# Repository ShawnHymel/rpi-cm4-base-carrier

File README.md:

# Raspberry Pi Compute Module 4 (CM4) Base Carrier

Simple carrier board for the Raspberry Pi Compute Module 4. It provides power to the module through the USB-C connector (power only, no data), USB client mode (host mode is not supported), Qwiic/Stemma connector for I2C lines, SPI, UART, and power/activity LEDs.

Feel free to modify this design for your own application. This PCB is not intended to be an end product but rather a demo to get people started making their own carrier boards for the CM4.

Note that USB traces were calculated for a 2-layer board with a 1.6mm height.

## License

Schematic and PCB layout files are licensed under the [CC BY 4.0](https://creativecommons.org/licenses/by/2.0/) license.

Individual components and footprints found in the CM4IO library are licensed as per the Design Files license found [here](https://datasheets.raspberrypi.org/license.html).

THE DESIGN IS PROVIDED "AS IS" AND THE AUTHOR DISCLAIMS ALL WARRANTIES WITH REGARD TO THIS DESIGN INCLUDING ALL IMPLIED WARRANTIES OF MERCHANTABILITY AND FITNESS. IN NO EVENT SHALL THE AUTHOR BE LIABLE FOR ANY SPECIAL, DIRECT, INDIRECT, OR CONSEQUENTIAL DAMAGES OR ANY DAMAGES WHATSOEVER RESULTING FROM LOSS OF USE, DATA OR PROFITS, WHETHER IN AN ACTION OF CONTRACT, NEGLIGENCE OR OTHER TORTIOUS ACTION, ARISING OUT OF OR IN CONNECTION WITH THE USE OR PERFORMANCE OF THIS DESIGN.

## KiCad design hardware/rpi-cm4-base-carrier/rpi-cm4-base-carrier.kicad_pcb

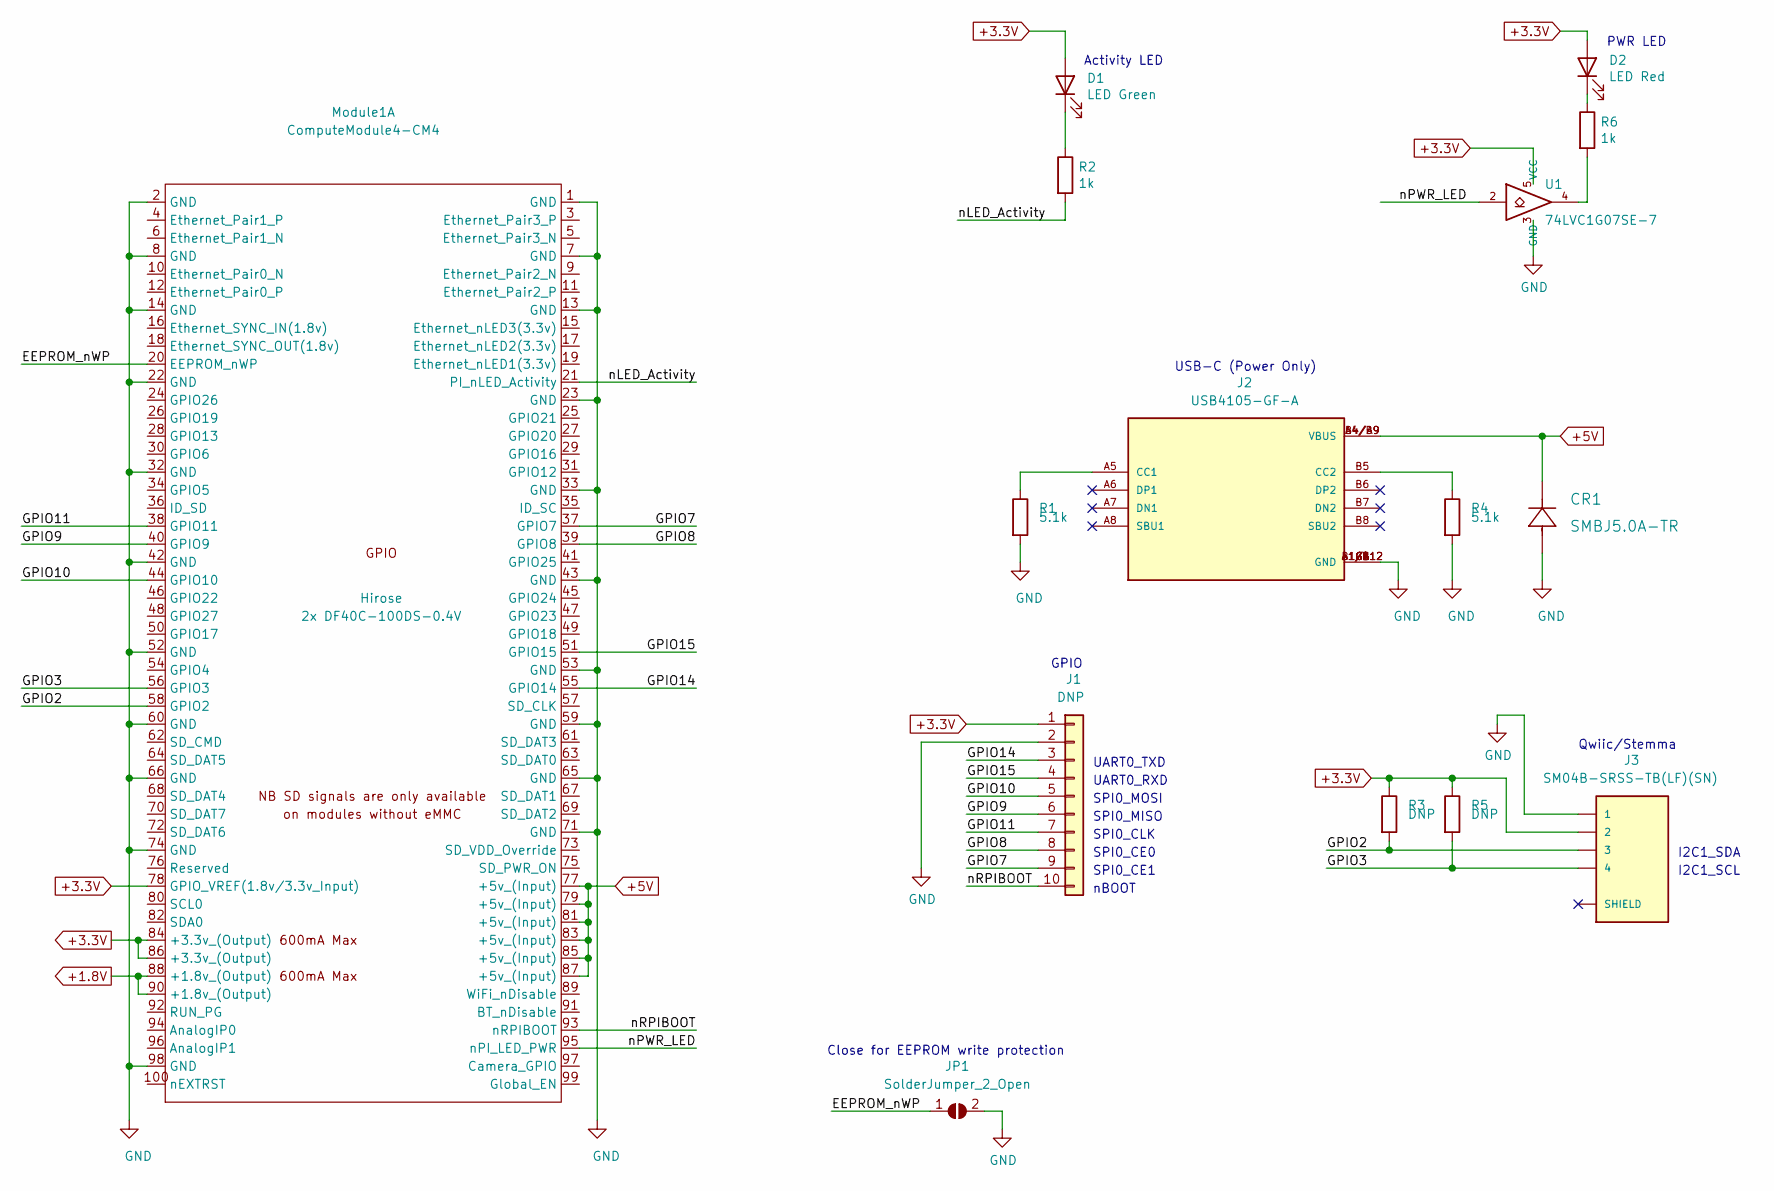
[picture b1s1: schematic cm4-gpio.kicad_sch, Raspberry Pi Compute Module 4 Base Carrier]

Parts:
CR1: SMBJ5.0A-TR; MPN SMBJ5.0A-TR; Digi-Key_PN 497-3144-1-ND
D1: LED Green; LED_0603_1608Metric; Part Description Green 572nm LED Indication - Discrete 2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; Digi-Key_PN 160-1478-1-ND
D2: LED Red; LED_0603_1608Metric; Part Description Red 620nm LED Indication - Discrete 2.2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; Digi-Key_PN 160-1479-1-ND
J1: DNP; PinHeader_1x10_P2.54mm_Vertical
J2: USB4105-GF-A; GCT_USB4105-GF-A; MPN USB4105-GF-A; Digi-Key_PN 2073-USB4105-GF-ACT-ND
J3: SM04B-SRSS-TB(LF)(SN); JST_SM04B-SRSS-TB(LF)(SN); MPN SM04B-SRSS-TB(LF)(SN); Digi-Key_PN 455-1804-1-ND
JP1: SolderJumper_2_Open; SolderJumper-2_P1.3mm_Open_RoundedPad1.0x1.5mm
Module1: ComputeModule4-CM4; Raspberry-Pi-4-Compute-Module; MPN 2x DF40C-100DS-0.4V; Digi-Key_PN 2x H11615CT-ND
R1, R4: 5.1k; R_0603_1608Metric_Pad0.98x0.95mm_HandSolder; MPN RC0603FR-075K1L; Digi-Key_PN 311-5.10KHRCT-ND
R2, R6: 1k; R_0603_1608Metric_Pad0.98x0.95mm_HandSolder; MPN RC0603FR-071KL; Digi-Key_PN 311-1.00KHRCT-ND
R3, R5: DNP; R_0603_1608Metric_Pad0.98x0.95mm_HandSolder
U1: 74LVC1G07SE-7; SOT-353_SC-70-5; Part Description Buffer, Non-Inverting 1 Element 1 Bit p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; Digi-Key_PN 74LVC1G07SE-7DICT-ND

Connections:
+1.8V: Module1.88 (+1.8v_(Output)), Module1.90 (+1.8v_(Output))
+3.3V: D1.2 (A), D2.2 (A), J1.1, J3.2, Module1.78 (GPIO_VREF(1.8v/3.3v_Input)), Module1.84 (+3.3v_(Output)), Module1.86 (+3.3v_(Output)), R3.1, R5.1, U1.5 (VCC)
+5V: CR1.1, J2.A4/B9 (VBUS), J2.B4/A9 (VBUS), Module1.77 (+5v_(Input)), Module1.79 (+5v_(Input)), Module1.81 (+5v_(Input)), Module1.83 (+5v_(Input)), Module1.85 (+5v_(Input)), Module1.87 (+5v_(Input))
/CM4 GPIO/EEPROM_nWP: JP1.1 (A), Module1.20 (EEPROM_nWP)
/CM4 GPIO/GPIO2: J3.3, Module1.58 (GPIO2), R3.2
/CM4 GPIO/GPIO3: J3.4, Module1.56 (GPIO3), R5.2
/CM4 GPIO/GPIO7: J1.9, Module1.37 (GPIO7)
/CM4 GPIO/GPIO8: J1.8, Module1.39 (GPIO8)
/CM4 GPIO/GPIO9: J1.6, Module1.40 (GPIO9)
/CM4 GPIO/GPIO10: J1.5, Module1.44 (GPIO10)
/CM4 GPIO/GPIO11: J1.7, Module1.38 (GPIO11)
/CM4 GPIO/GPIO14: J1.3, Module1.55 (GPIO14)
/CM4 GPIO/GPIO15: J1.4, Module1.51 (GPIO15)
/CM4 GPIO/nLED_Activity: Module1.21 (PI_nLED_Activity), R2.2
/CM4 GPIO/nPWR_LED: Module1.95 (nPI_LED_PWR), U1.2
/CM4 GPIO/nRPIBOOT: J1.10, Module1.93 (nRPIBOOT)
GND: CR1.2, J1.2, J2.A1/B12 (GND), J2.B1/A12 (GND), J2.G1 (GND), J2.G2 (GND), J2.G3 (GND), J2.G4 (GND), J3.1, JP1.2 (B), Module1.1 (GND), Module1.2 (GND), Module1.7 (GND), Module1.8 (GND), Module1.13 (GND), Module1.14 (GND), Module1.22 (GND), Module1.23 (GND), Module1.32 (GND), Module1.33 (GND), Module1.42 (GND), Module1.43 (GND), Module1.52 (GND), Module1.53 (GND), Module1.59 (GND), Module1.60 (GND), Module1.65 (GND), Module1.66 (GND), Module1.71 (GND), Module1.74 (GND), Module1.98 (GND), R1.2, R4.2, U1.3 (GND); also elsewhere on the board
unnamed: D1.1 (K), R2.1
unnamed: D2.1 (K), R6.1
unnamed: J2.A5 (CC1), R1.1
unnamed: J2.B5 (CC2), R4.1
unnamed: J3.S1 (SHIELD), J3.S2 (SHIELD)
unnamed: R6.2, U1.4

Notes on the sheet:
Close for EEPROM write protection
Activity LED
GPIO
UART0_TXD
UART0_RXD
SPI0_MOSI
SPI0_MISO
SPI0_CLK
SPI0_CE0
SPI0_CE1
nBOOT
USB-C (Power Only)
PWR LED
Qwiic/Stemma
I2C1_SDA
I2C1_SCL

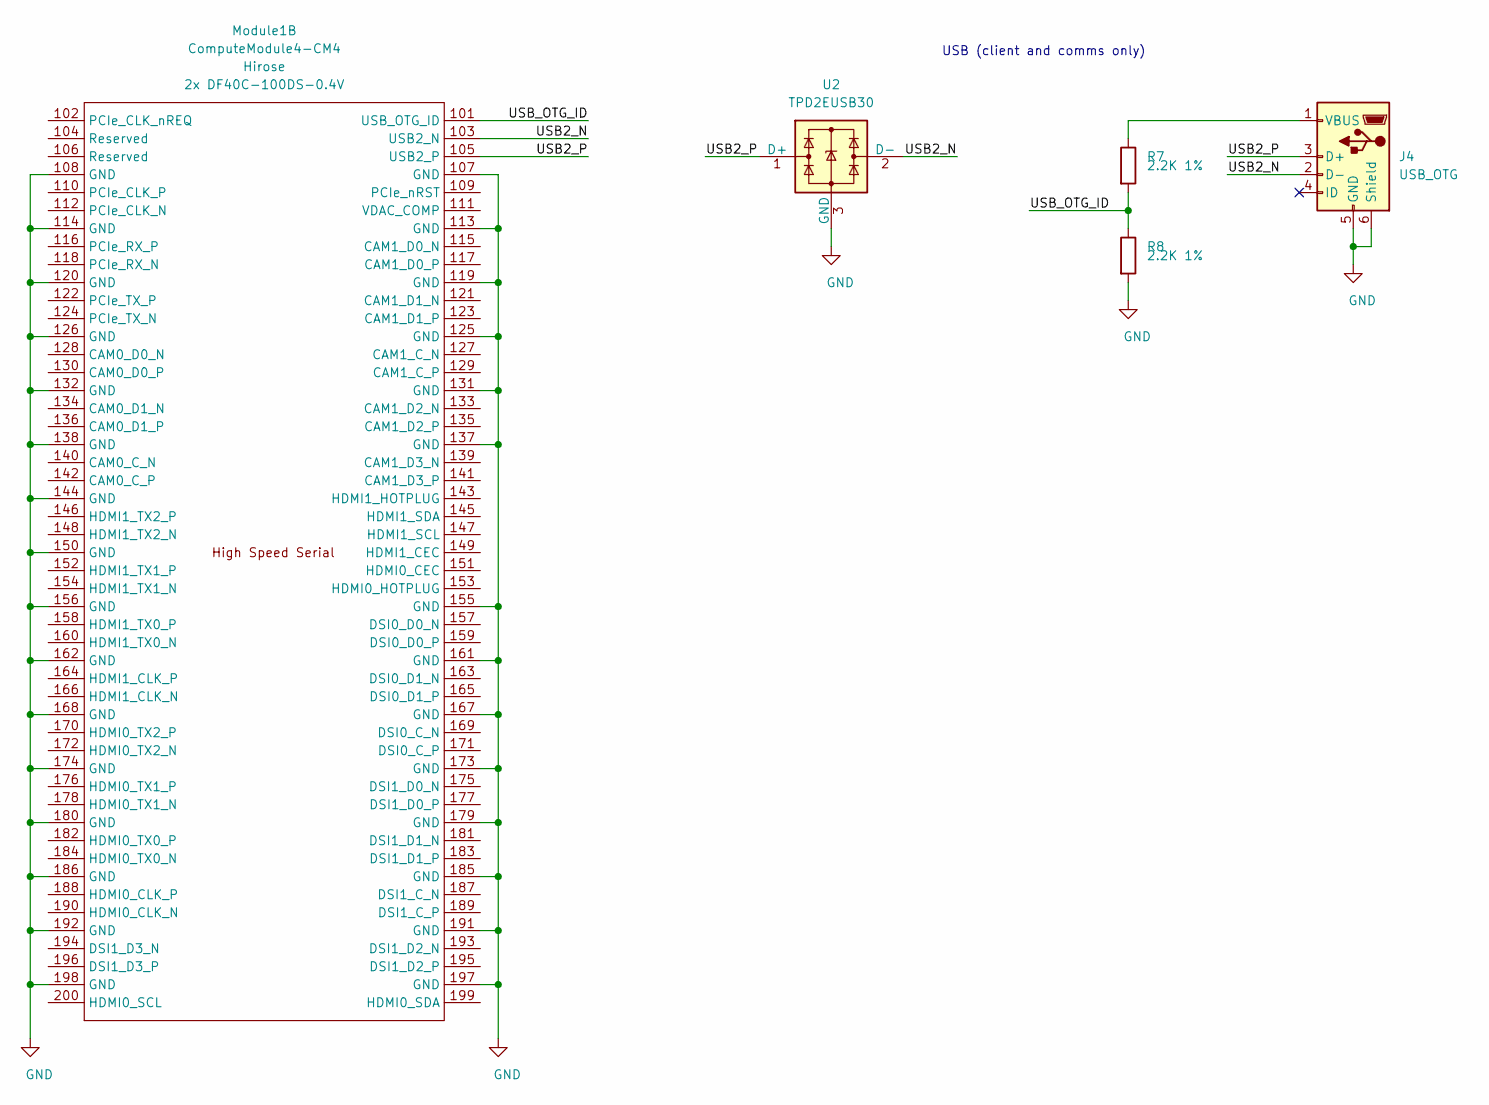
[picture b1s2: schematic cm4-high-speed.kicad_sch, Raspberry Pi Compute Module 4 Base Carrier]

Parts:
J4: USB_OTG; USB_Micro-B_EDAC_UCON00686; MPN 10103594-0001LF; Digi-Key_PN 609-4050-1-ND
Module1: ComputeModule4-CM4; Raspberry-Pi-4-Compute-Module; Digi-Key_PN 2x H11615CT-ND
R7, R8: 2.2K 1%; R_0603_1608Metric_Pad0.98x0.95mm_HandSolder; MPN RC0603FR-072K2L; Digi-Key_PN 311-2.20KHRCT-ND
U2: TPD2EUSB30; Texas_DRT-3; MPN TPD2EUSB30DRTR; Digi-Key_PN 296-25509-1-ND

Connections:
/CM4 High Speed/USB2_N: J4.2 (D-), Module1.103 (USB2_N), U2.2 (D-)
/CM4 High Speed/USB2_P: J4.3 (D+), Module1.105 (USB2_P), U2.1 (D+)
/CM4 High Speed/USB_OTG_ID: Module1.101 (USB_OTG_ID), R7.2, R8.1
GND: J4.5 (GND), J4.6 (Shield), Module1.107 (GND), Module1.108 (GND), Module1.113 (GND), Module1.114 (GND), Module1.119 (GND), Module1.120 (GND), Module1.125 (GND), Module1.126 (GND), Module1.131 (GND), Module1.132 (GND), Module1.137 (GND), Module1.138 (GND), Module1.144 (GND), Module1.150 (GND), Module1.155 (GND), Module1.156 (GND), Module1.161 (GND), Module1.162 (GND), Module1.167 (GND), Module1.168 (GND), Module1.173 (GND), Module1.174 (GND), Module1.179 (GND), Module1.180 (GND), Module1.185 (GND), Module1.186 (GND), Module1.191 (GND), Module1.192 (GND), Module1.197 (GND), Module1.198 (GND), R8.2, U2.3 (GND); also elsewhere on the board
unnamed: J4.1 (VBUS), R7.1

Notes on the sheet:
USB (client and comms only)

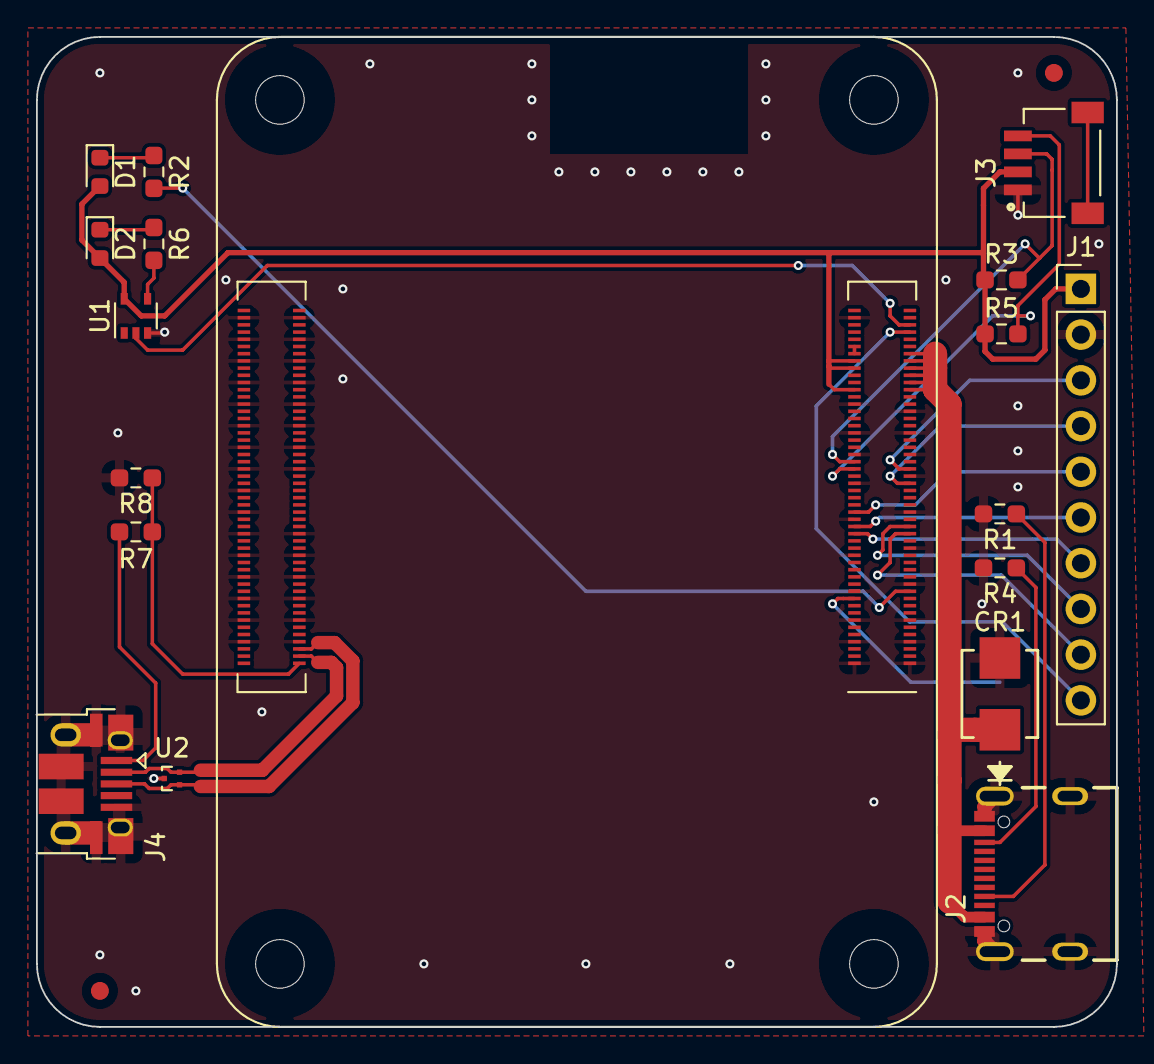
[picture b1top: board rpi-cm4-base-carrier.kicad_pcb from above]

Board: 2 copper layers, 60.0 x 55.0 mm, 19 parts (1 on the bottom side), 27 nets.

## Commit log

2020-11-06 Added USB connectors
2020-11-07 Finished schematic
2020-11-07 Added labels to schematic sections
2020-11-09 Placed components
2020-11-12 Pretended to route USB lines
2020-11-13 Finished with PCB layout
2020-11-21 Added rendered image. Updated readme.
2021-05-14 Added BOM

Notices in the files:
hardware/rpi-cm4-base-carrier/cm4-gpio.kicad_sch:
creativecommons.org/licenses/by-sa/4.0
License: CC BY-SA 4.0
hardware/rpi-cm4-base-carrier/rpi-cm4-base-carrier.kicad_pcb:
creativecommons.org/licenses/by/4.0
parts and their libraries:
Copyright 2016 Accelerated Designs. All rights reserved.
